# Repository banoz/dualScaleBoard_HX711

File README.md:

# Dual HX711 scales interface board

Top layer

Bottom layer

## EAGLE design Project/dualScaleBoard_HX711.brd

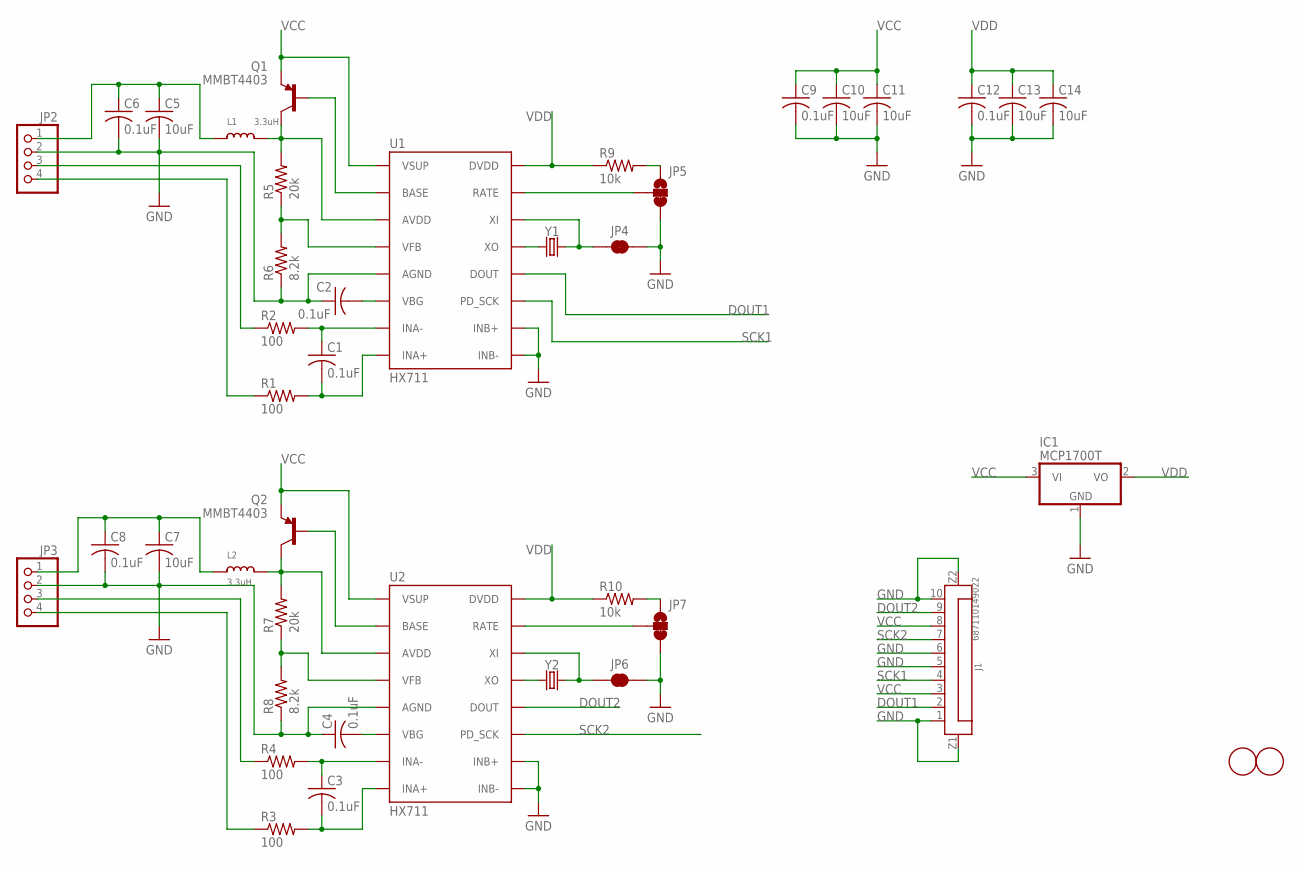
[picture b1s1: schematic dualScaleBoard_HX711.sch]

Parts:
C1, C2, C3, C4, C6, C8, C9, C12: 0.1uF; C0603; LCSC C1591
C5, C7, C10, C11, C13, C14: 10uF; C0603; LCSC C19702
IC1: MCP1700T; SOT23; LCSC C39051
J1: 687110149022; LCSC C127355
JP2, JP3: PINHD-1X4; 1X04
JP4, JP6: JUMPER-SMT_2_NC_TRACE_SILK; SMT-JUMPER_2_NC_TRACE_SILK
JP5, JP7: JUMPER-SMT_3_1-NC_TRACE_SILK; SMT-JUMPER_3_1-NC_TRACE_SILK
L1, L2: 3.3uH; _0603; LCSC C275346
Q1, Q2: MMBT4403; SOT23-3; LCSC C78864
R1, R2, R3, R4: 100; R0402; LCSC C328416
R5, R7: 20k; R0402; LCSC C351700
R6, R8: 8.2k; R0402; LCSC C517526
R9, R10: 10k; R0402; LCSC C317926
U1, U2: HX711; SO16; LCSC C43656
U$1, U$2: FIDUCIAL; FIDUCIAL_1MM
Y1, Y2: CRYSTALSMD-5X3.2-4PAD; CRYSTAL-SMD-5X3.2-4PAD

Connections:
DOUT1: J1.2, U1.12 (DOUT)
DOUT2: J1.9, U2.12 (DOUT)
GND: C2.1, C4.1, C5.2, C6.2, C7.2, C8.2, C9.2, C10.2, C11.2, C12.2, C13.2, C14.2, IC1.1 (GND), J1.1, J1.5, J1.6, J1.10, J1.Z1, J1.Z2, JP2.2, JP3.2, JP4.2, JP5.3, JP6.2, JP7.3, R6.1, R8.1, U1.5 (AGND), U1.9 (INB-), U1.10 (INB+), U2.5 (AGND), U2.9 (INB-), U2.10 (INB+)
unnamed: C2.2, U1.6 (VBG)
unnamed: R5.1, R6.2, U1.4 (VFB)
unnamed: L1.2, Q1.3 (C), R5.2, U1.3 (AVDD)
unnamed: C1.1, R2.2, U1.7 (INA-)
unnamed: Q1.1 (B), U1.2 (BASE)
unnamed: C1.2, R1.2, U1.8 (INA+)
unnamed: JP2.3, R2.1
unnamed: JP2.4, R1.1
unnamed: C5.1, C6.1, JP2.1, L1.1
unnamed: C3.1, R4.2, U2.7 (INA-)
unnamed: C3.2, R3.2, U2.8 (INA+)
unnamed: U1.13 (XO), Y1.1
unnamed: C4.2, U2.6 (VBG)
unnamed: R7.1, R8.2, U2.4 (VFB)
unnamed: C7.1, C8.1, JP3.1, L2.1
unnamed: L2.2, Q2.3 (C), R7.2, U2.3 (AVDD)
unnamed: JP3.3, R4.1
unnamed: Q2.1 (B), U2.2 (BASE)
unnamed: JP3.4, R3.1
unnamed: U2.13 (XO), Y2.1
unnamed: JP4.1, U1.14 (XI), Y1.3 (2)
unnamed: JP5.2, U1.15 (RATE)
unnamed: JP5.1, R9.2
unnamed: JP6.1, U2.14 (XI), Y2.3 (2)
unnamed: JP7.2, U2.15 (RATE)
unnamed: JP7.1, R10.2
SCK1: J1.4, U1.11 (PD_SCK)
SCK2: J1.7, U2.11 (PD_SCK)
VCC: C9.1, C10.1, C11.1, IC1.3 (VI), J1.3, J1.8, Q1.2 (E), Q2.2 (E), U1.1 (VSUP), U2.1 (VSUP)
VDD: C12.1, C13.1, C14.1, IC1.2 (VO), R9.1, R10.1, U1.16 (DVDD), U2.16 (DVDD)

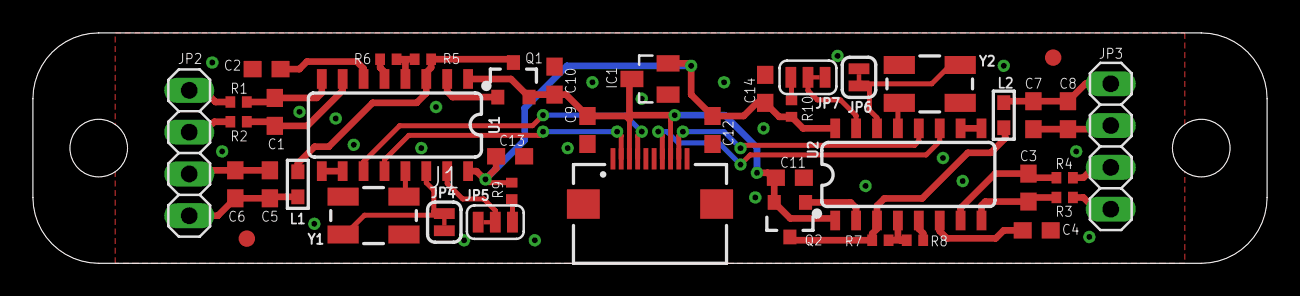
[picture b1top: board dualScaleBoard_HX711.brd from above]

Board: 2 copper layers, 75.0 x 14.0 mm, 43 parts (1 on the bottom side), 33 nets.

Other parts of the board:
U$3: ESD_10.00

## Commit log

2022-01-27 Create LICENSE
2022-01-27 Initial state
2022-02-10 BOM update
2022-04-27 VDD LDO option
2022-05-03 pin reassignment
2023-11-30 FPC version
2025-02-21 FPC adaptor

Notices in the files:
parts and their libraries:
SparkFun-Jumpers: Licensing: Creative Commons ShareAlike 4.0 International - https://creativecommons.org/licenses/by-sa/4.0
microbuilder: This work is placed in the public domain, and may be freely used for commercial and non-commercial work with the following conditions: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
